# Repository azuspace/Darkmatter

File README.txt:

Darkmatter is the world's first laser-cut, 3D printed Xbox Laptop. For more info please visit the following links:

Site:
http://photongaming.com/

Kickstarter Link:
http://www.kickstarter.com/projects/1360501894/darkmatter-xbox-laptop-and-diy-kit

Darkmatter forum at:
http://techjango.com

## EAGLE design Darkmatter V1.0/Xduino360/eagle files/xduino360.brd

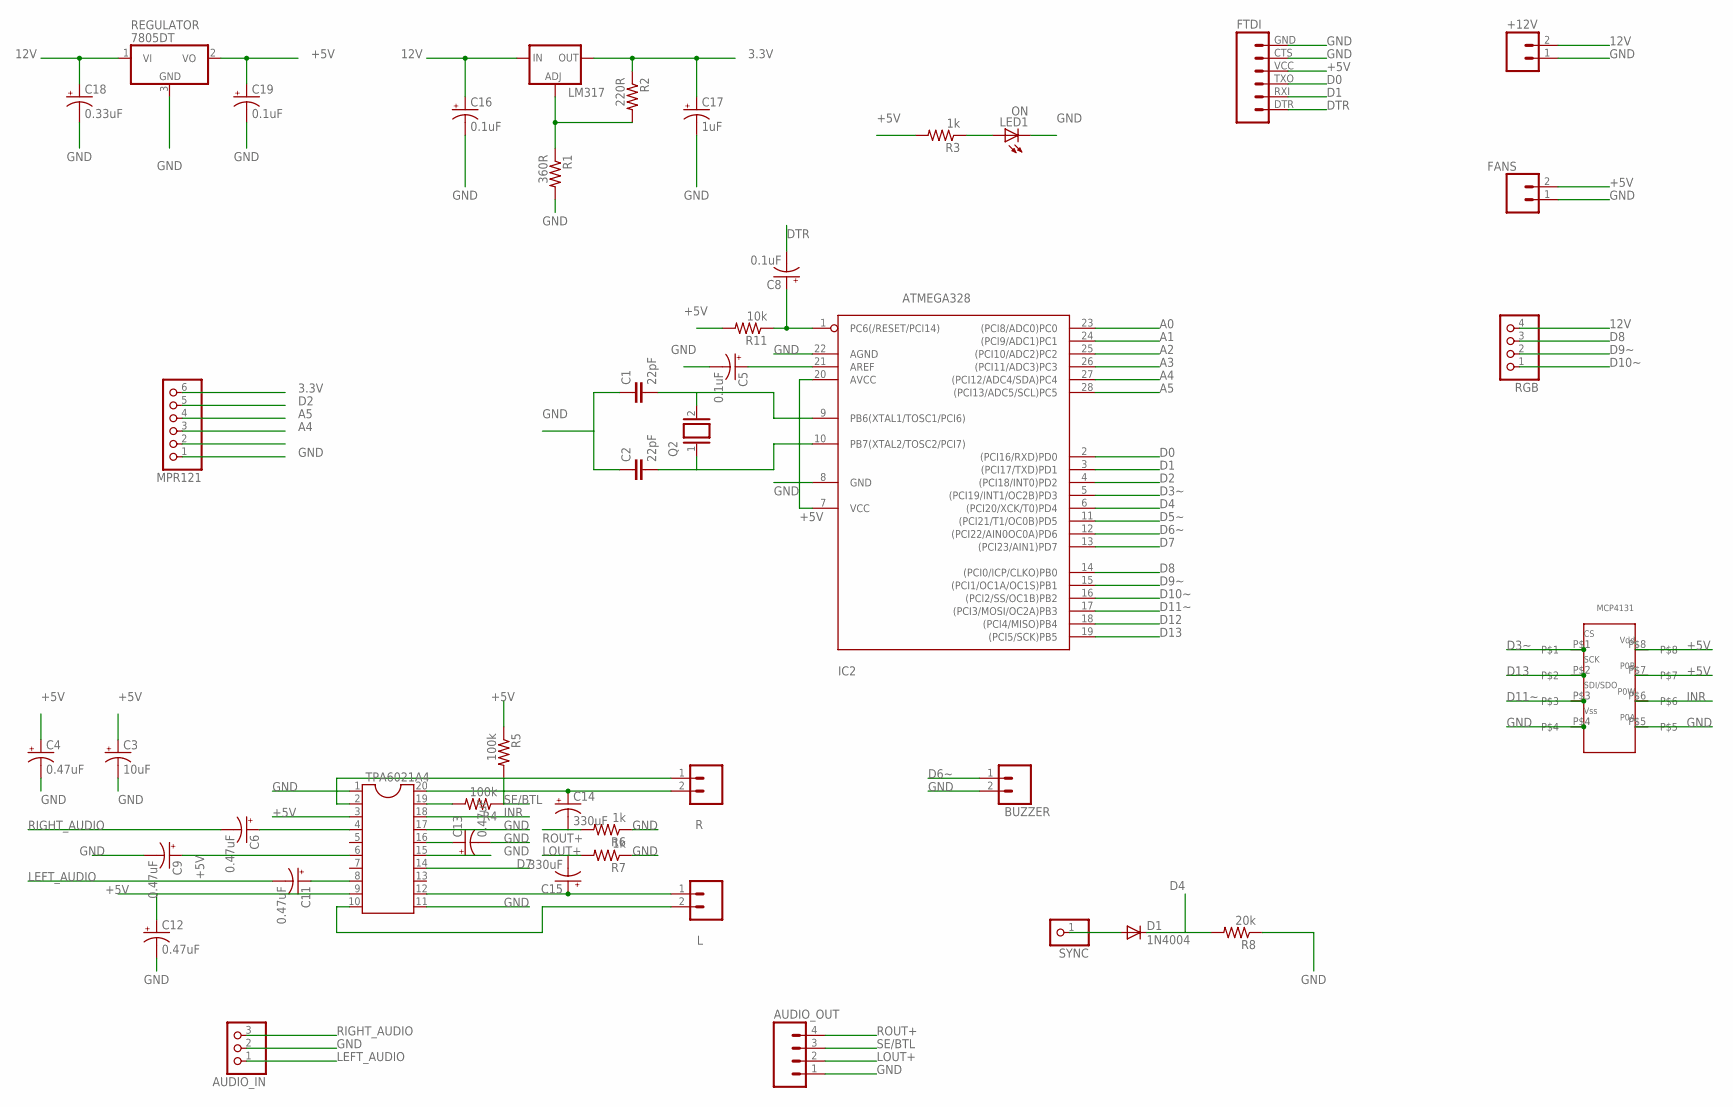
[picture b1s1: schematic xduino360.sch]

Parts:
+12V: M02PTH; 1X02
AUDIO_IN: PINHD-1X3; 1X03
AUDIO_OUT: M04PTH; 1X04
BUZZER: M02PTH; 1X02
C1, C2: 22pF; C5B2.5
C3: 10uF; TT2D5
C4, C6, C9, C11, C12, C13: 0.47uF; TT2D5
C5, C8, C16, C19: 0.1uF; TT2D5
C14, C15: 330uF; TT2D5
C17: 1uF; TT2D5
C18: 0.33uF; TT2D5
D1: 1N4004; DO41-10
FANS: M02PTH; 1X02
FTDI: FTDI_BASICPTH; FTDI_BASIC
IC2: ATMEGA328; DIL28-3
L: M02PTH; 1X02
LED1: ON; LED3MM
LM317: V_REG_317DPACK; V-REG_DPACK
MCP4131: MCP4131
MPR121: PINHD-1X6; 1X06
Q2: XTAL/S; QS
R: M02PTH; 1X02
R1: 360R; 0204V
R2: 220R; 0204V
R3, R6, R7: 1k; 0204V
R4, R5: 100k; 0204V
R8: 20k; 0204V
R11: 10k; 0204V
REGULATOR: 7805DT; TO252
RGB: PINHD-1X4; 1X04
SYNC: PINHD-1X1; 1X01
TPA6021A4: DIL20

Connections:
3.3V: C17.+, LM317.4 (OUT), MPR121.6, R2.1
12V: +12V.2, C16.+, C18.+, LM317.3 (IN), REGULATOR.1 (VI), RGB.4
+5V: C3.+, C4.+, C9.+, C12.+, C19.+, FANS.2, FTDI.VCC (4), IC2.7 (VCC), IC2.20 (AVCC), MCP4131.P$7, MCP4131.P$8, R3.2, R5.1, R11.2, REGULATOR.2 (VO), TPA6021A4.3, TPA6021A4.6, TPA6021A4.9
A0: IC2.23 ((PCI8/ADC0)PC0)
A1: IC2.24 ((PCI9/ADC1)PC1)
A2: IC2.25 ((PCI10/ADC2)PC2)
A3: IC2.26 ((PCI11/ADC3)PC3)
A4: IC2.27 ((PCI12/ADC4/SDA)PC4), MPR121.3
A5: IC2.28 ((PCI13/ADC5/SCL)PC5), MPR121.4
D0: FTDI.TXO (3), IC2.2 ((PCI16/RXD)PD0)
D1: FTDI.RXI (2), IC2.3 ((PCI17/TXD)PD1)
D2: IC2.4 ((PCI18/INT0)PD2), MPR121.5
D3~: IC2.5 ((PCI19/INT1/OC2B)PD3), MCP4131.P$1
D4: D1.C, IC2.6 ((PCI20/XCK/T0)PD4), R8.2
D5~: IC2.11 ((PCI21/T1/OC0B)PD5)
D6~: BUZZER.1, IC2.12 ((PCI22/AIN0OC0A)PD6)
D7: IC2.13 ((PCI23/AIN1)PD7), TPA6021A4.14
D8: IC2.14 ((PCI0/ICP/CLKO)PB0), RGB.3
D9~: IC2.15 ((PCI1/OC1A/OC1S)PB1), RGB.2
D10~: IC2.16 ((PCI2/SS/OC1B)PB2), RGB.1
D11~: IC2.17 ((PCI3/MOSI/OC2A)PB3), MCP4131.P$3
D12: IC2.18 ((PCI4/MISO)PB4)
D13: IC2.19 ((PCI5/SCK)PB5), MCP4131.P$2
DTR: C8.-, FTDI.DTR (1)
GND: +12V.1, AUDIO_IN.2, AUDIO_OUT.1, BUZZER.2, C1.1, C2.1, C3.-, C4.-, C5.-, C9.-, C12.-, C13.-, C16.-, C17.-, C18.-, C19.-, FANS.1, FTDI.CTS (5), FTDI.GND (6), IC2.8 (GND), IC2.22 (AGND), LED1.K (C), MCP4131.P$4, MCP4131.P$5, MPR121.1, R1.2, R6.1, R7.1, R8.1, REGULATOR.3 (GND), TPA6021A4.1, TPA6021A4.11, TPA6021A4.15, TPA6021A4.17
INR: MCP4131.P$6, TPA6021A4.18
LEFT_AUDIO: AUDIO_IN.1, C11.-
LOUT+: AUDIO_OUT.2, C15.-, R7.2
unnamed: LM317.1 (ADJ), R1.1, R2.2
unnamed: C8.+, IC2.1 (PC6(/RESET/PCI14)), R11.1
unnamed: C2.2, IC2.10 (PB7(XTAL2/TOSC2/PCI7)), Q2.1
unnamed: C6.+, TPA6021A4.4
unnamed: C1.2, IC2.9 (PB6(XTAL1/TOSC1/PCI6)), Q2.2
unnamed: C5.+, IC2.21 (AREF)
unnamed: C11.+, TPA6021A4.8
unnamed: R.1, TPA6021A4.2
unnamed: C13.+, TPA6021A4.16
unnamed: R4.2, TPA6021A4.19
unnamed: C14.+, R.2, TPA6021A4.20
unnamed: C15.+, L.1, TPA6021A4.12
unnamed: L.2, TPA6021A4.10
unnamed: D1.A, SYNC.1
unnamed: LED1.A, R3.1
RIGHT_AUDIO: AUDIO_IN.3, C6.-
ROUT+: AUDIO_OUT.4, C14.-, R6.2
SE/BTL: AUDIO_OUT.3, R4.1, R5.2

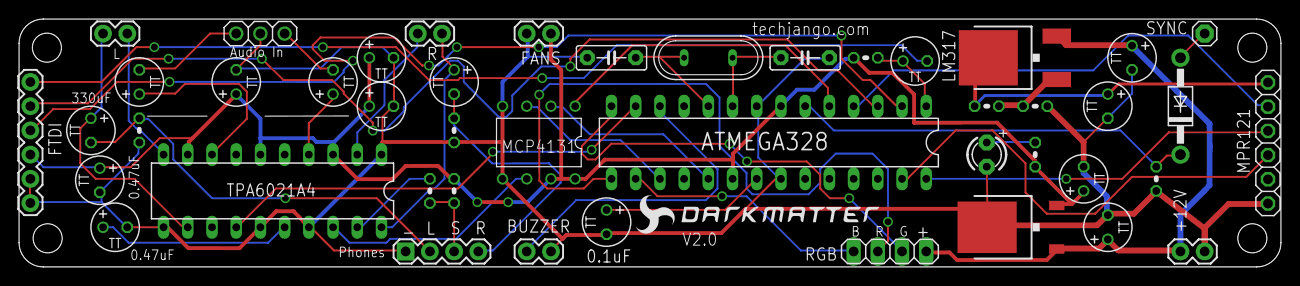
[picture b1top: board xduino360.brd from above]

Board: 4 copper layers, 132.4 x 26.0 mm, 49 parts (0 on the bottom side), 40 nets.

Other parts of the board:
U$1, U$2, U$3, U$4: STAND-OFF-TIGHT

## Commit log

2013-10-24 First version of Darkmatter manual uploaded
2013-11-12 3D STL Files
    CAD STL files generated from Autodesk Inventor
2013-12-06 Added xduino360 files
2014-01-24 Added acrylic CDR files
2014-03-03 Added Manual v0.92
2014-03-03 Create gh-pages branch via GitHub
2014-03-03 tests
2014-03-03 added manual
2014-03-03 miscellaneous changes
2014-03-03 html changes
2014-03-03 renaming
2014-03-03 renaming for tidiness
2014-03-31 manual ver .93
2014-05-13 ver .94

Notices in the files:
parts and their libraries:
SparkFun-Connectors: Licensing: CC v3.0 Share-Alike You are welcome to use this library for commercial purposes.
